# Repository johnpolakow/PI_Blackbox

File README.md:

# Raspberry Pi Based Data Acquistion System

# Directories in Repository    
## Docs/    
Contains various documentation info  created while building the software. Specification of commands to the client interface. Information on the ADC Loop, which is continuosly read out by the Raspberry Pi. Some notes on initial configuration of a Pi DAQ. Some how to files that may be useful while administrating the Pi DAQ.

## PCB/    
PI DAQ PCB Files    
Contains the files needed to FAB the Pi DAQ. All Gerber board files are present. The native Kicad project files are present as well, for maintenance and modification. There is rework required for the version of gerbers used here. The rework directions are in the **Docs/** folder. If time permits, will include a "fixed/corrected" version of the Kicad project files, eliminating the need for future rework. 

Cal Station Board Files
The PCB files for the Cal Station board are present as well, however I would not reccomend ordering this board. It was done extremely quickly and many mistakes were made. There was MUCH rework required to make the PCB functional. Almost all of the relay footprints are off. The relay part fits, but some of the pins are swapped. It was unpleasant to re-route all the signals with hookup wire, you would save yourself much time by starting over.    

All BOMS should be present as well.    

## Pi Firmware/
This folder contains the release versions of firmware that runs on the Pi DAQ. The different versions are kept for documentation and bug fixes. Also, the Configuration folder contains useful code to configure a Pi for the first time. It performs functions like:
  - Configuring hostname on the Pi
  - Configure user accounts
  - Getting / Setting Environment variables
  - Setting up alias commands for the pi user
  - setting default IP address and network configuration
  - Enabling SPI & I2C on the pi
  - Enabling SSH
  - Enable AutoLogin at boot for user pi
  - Getting the micro SD card usage stats

# Code Installation and Usage
## Source Code Download 
To download the code to the Pi, make sure you have an active internet connection on the Pi. This may involve editing the /etc/wpa_supplicant/wpa_supplicant.conf file on the Pi to add the credentials for the wifi network you want to connect to. The file will look like this:    
   
modify it by filling in the ssid of the network and the pre shared key (password) of the network.   

After conneting to Wifi/Internet, make a directory for the firmware:   
```mkdir /home/pi/firmware```   
```cd /home/pi/firmware```    
    
now clone the github repo:   
```git clone https://github.com/johnpolakow/PI_Blackbox.git```       

move everything to parent folder:         
```cd PI_Blackbox/```      
```mv -f ./* ../```     
```cd ..```
```rm -rf PI_Blackbox/```    

The PCB directory is not needed on the Pi:     
```rm -rf PCB/```     

move Docs folder to parent dir:    
```mv -f Docs/ ../```   

Change to Pi_Firmware directory and remove unnecesary releases, and move Configuration directory:      
```cd PI_Firmware/```     

Only the latest version is needed. You can remove the directories for older versions. For instance if you want to remove *Release0/* directory:    
```rm -rf Release0/```    

Move **Configuration/** directory to another location:    
```mv Configuration/ ../../```      

Last, the contents of the latest release may be moved to the firmware folder:    
```cd Release1```       
```mv -f ./* ../../```    
```cd ..```    
```rm -r Release1```    
```rm -r PI_Firmware/```     

You should now have two items in the **/home/pi/firmware/** folder:     
  - src/ folder, containing source code for compiling the DAQ executable    
  - makefile, to compile the source code    

## Compilation    
Compile the source code with the **make** command:    

the **DAQ** binary will be created. It can be executed directly with the command:     
```sudo ./DAQ```     

or, alternatively, the server process can be started with:     
```sudo systemctl restart Blackberry.service```    

check to see the process is running with the **top** command:   
```top```     
after executing the command a process display will popup. **DAQ** should be at the top:    
   
to exit out of the process display screen, hit the **q** button 

If DAQ process is not shown, then you need to either execute the DAQ process directly or start the Blackberry systemd service with:   
```sudo systemctl start Blackberry.service```

## SystemD Maintenance and Server Process Start     
 Some commands to administrate the Blackberry server process.
 see process status:        
```sudo systemctl status Blackberry.service```     

start the process:   
```sudo systemctl start Blackberry.service```    

stop the process:   
```sudo systemctl stop Blackberry.service```    

to start service at boot:    
```sudo systemctl enable [Blackberry.service]```    

view the server process file:   
```sudo systemctl cat Blackberry.service```

edit the service file:    
```sudo systemctl edit --full Blackberry.service```   

find out if the service is enabled:   
```sudo systemctl is-enabled Blackberry.service```

see log entries related only the the PI DAQ server process:   
```sudo journalctl UNIT=Blackberry.service```

```daemon-reload```

## Socket Connections    
The DAQ process opens tcp port 2020 and waits for a client to connect. To verify the port is open and listening, try these commands:    
```sudo ss -l -p | grep -vE '^(u_|nl )'```   
```sudo ss -lntu```    
```netstat -l -46```    

## Querying the Server from a Client Machine
see client code repository. Also see 'Pi_Blackbox_Software_Behavioral_Specification' in the Docs/ directory:   
https://github.com/johnpolakow/PI_Blackbox/tree/master/Docs        
https://github.com/johnpolakow/PI_Blackbox/blob/master/Docs/Pi%20Blackbox%20Software%20Behavioral%20Specification_v2.pdf     
https://github.com/johnpolakow/Blackbox_Client    

## Lessons Learned
Things I would do differently if I was to do another version of this board:     
  - Do the layout in Cadence
  - Use switching regulator to drop input of +18-24V down to +13-14V. Eliminating the need for fan and heat sink
  - Low noise *switching* regulator for Pi voltage supply. The present switching converter IC required softening of the switching waveform to get the noise down.
  - Change 2N3055 BJT based programmable current source to FET based. 
  - smaller SMD crystals
  - Use SOM instead of full Pi Board
  - High speed ADCs for Voltage and Current measurement. More accurate power metric + phase information
  - More compact electrolytic caps
  - Only use ceramic caps near LT1054 voltage inverter. Tantalum cap ended up failing due to high ESR and switching current
  - smaller input capacitance, to lower the inrush current

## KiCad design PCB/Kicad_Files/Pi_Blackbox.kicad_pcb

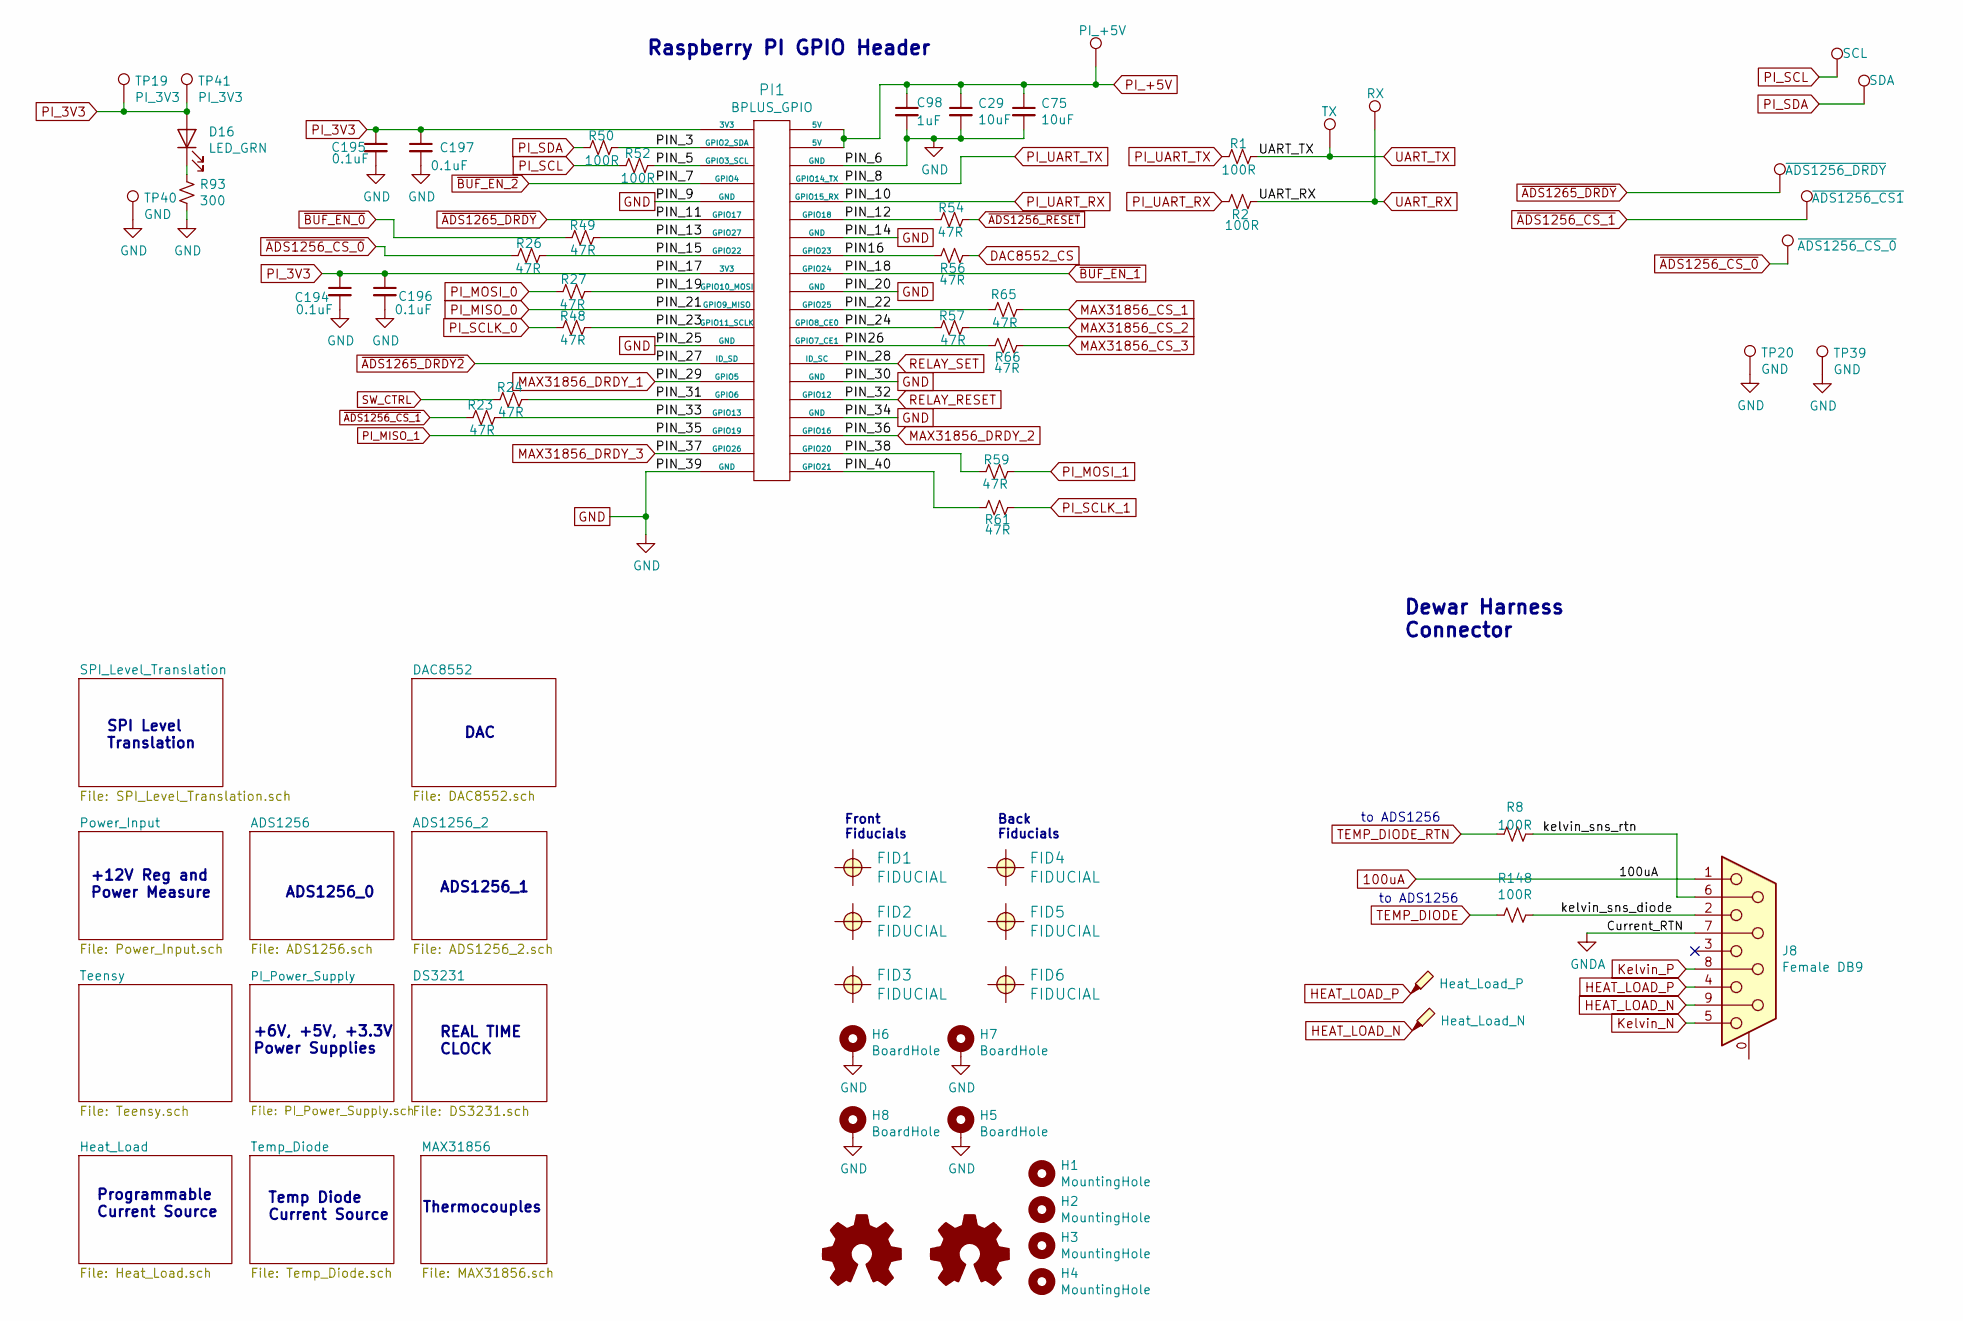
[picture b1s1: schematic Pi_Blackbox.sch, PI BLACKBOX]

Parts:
C29, C75: 10uF; C_1206_3216Metric_Pad1.42x1.75mm_HandSolder
C98: 1uF; C_0603_1608Metric_Pad1.05x0.95mm_HandSolder
C194, C195, C196, C197: 0.1uF; C_0603_1608Metric_Pad1.05x0.95mm_HandSolder
D16: LED_GRN; LED_0805_2012Metric_Pad1.15x1.40mm_HandSolder
FID1, FID2, FID4, FID5: FIDUCIAL; Fiducial_0.5mm_Mask1.5mm
FID3: FIDUCIAL; Fiducial_1.5mm_Mask3mm
FID6: FIDUCIAL; Fiducial_0.75mm_Mask2.25mm
H1, H2, H3, H4: MountingHole; MountingHole_3.5mm_Pad_Via
H5, H6, H7, H8: BoardHole; MountingHole_2.7mm_M2.5_Pad_Via
J8: Female DB9; DB9_D09S13A4GX00LF
PI1: BPLUS_GPIO; PinHeader_2x20_P2.54mm_Vertical
R1, R2, R8, R50, R52, R148: 100R; R_0402_1005Metric
R23, R24, R26, R27, R48, R49, R54, R56, R57, R59, R61, R65, R66: 47R; R_0402_1005Metric
R93: 300; R_0402_1005Metric
TP1: TX; TestPoint_Pad_D2.0mm
TP2: RX; TestPoint_Pad_D2.0mm
TP3: SCL; TestPoint_SMT_Keystone_5190
TP4: ~ADS1256_CS_0; TestPoint_SMT_Keystone_5190
TP6: SDA; TestPoint_SMT_Keystone_5190
TP13: Heat_Load_P; TestPoint_SMT_Keystone_5190
TP14: ~ADS1256_DRDY; TestPoint_SMT_Keystone_5190
TP15: ~ADS1256_CS1; TestPoint_SMT_Keystone_5190
TP19: PI_3V3; TestPoint_SMT_Keystone_5190
TP20: GND; TestPoint_Keystone_5000-5004_Miniature
TP39: GND; TestPoint_Pad_D2.0mm
TP40: GND; TestPoint_SMT_Keystone_5190
TP41: PI_3V3; TestPoint_Pad_D2.0mm
TP42: PI_+5V; TestPoint_Pad_D2.0mm
TP43: Heat_Load_N; TestPoint_SMT_Keystone_5190

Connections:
100uA: J8.1; also elsewhere on the board
/PIN16: PI1.16 (GPIO23), R56.2
/PIN26: PI1.26 (GPIO7_CE1), R66.2
/PIN_3: PI1.3 (GPIO2_SDA), R50.1
/PIN_5: PI1.5 (GPIO3_SCL), R52.1
/PIN_12: PI1.12 (GPIO18), R54.2
/PIN_13: PI1.13 (GPIO27), R49.1
/PIN_15: PI1.15 (GPIO22), R26.1
/PIN_19: PI1.19 (GPIO10_MOSI), R27.1
/PIN_22: PI1.22 (GPIO25), R65.2
/PIN_23: PI1.23 (GPIO11_SCLK), R48.1
/PIN_24: PI1.24 (GPIO8_CE0), R57.2
/PIN_31: PI1.31 (GPIO6), R24.1
/PIN_33: PI1.33 (GPIO13), R23.1
/PIN_38: PI1.38 (GPIO20), R59.2
/PIN_40: PI1.40 (GPIO21), R61.2
/kelvin_sns_diode: J8.2, R148.1
/kelvin_sns_rtn: J8.6, R8.1
DAC8552_CS: R56.1; also elsewhere on the board
GND: C29.2, C75.2, C98.2, C194.2, C195.2, C196.2, C197.2, H5.PAD, H6.PAD, H7.PAD, H8.PAD, J8.5, J8.9, PI1.6 (GND), PI1.9 (GND), PI1.14 (GND), PI1.20 (GND), PI1.25 (GND), PI1.30 (GND), PI1.34 (GND), PI1.39 (GND), R93.2, TP20.1, TP39.1, TP40.1, TP43.1; also elsewhere on the board
GNDA: J8.7; also elsewhere on the board
HEAT_LOAD_P: J8.4, J8.8, TP13.1; also elsewhere on the board
MAX31856_CS_1: R65.1; also elsewhere on the board
MAX31856_CS_2: R57.1; also elsewhere on the board
MAX31856_CS_3: R66.1; also elsewhere on the board
MAX31856_DRDY_1: PI1.29 (GPIO5); also elsewhere on the board
MAX31856_DRDY_2: PI1.36 (GPIO16); also elsewhere on the board
MAX31856_DRDY_3: PI1.37 (GPIO26); also elsewhere on the board
unnamed: D16.1 (K), R93.1
PI_3V3: C194.1, C195.1, C196.1, C197.1, D16.2 (A), PI1.1 (3V3), PI1.17 (3V3), TP19.1, TP41.1
PI_+5V: C29.1, C75.1, C98.1, PI1.2 (5V), PI1.4 (5V), TP42.1; also elsewhere on the board
PI_MISO_0: PI1.21 (GPIO9_MISO); also elsewhere on the board
PI_MISO_1: PI1.35 (GPIO19); also elsewhere on the board
PI_MOSI_0: R27.2; also elsewhere on the board
PI_MOSI_1: R59.1; also elsewhere on the board
PI_SCL: R52.2, TP3.1; also elsewhere on the board
PI_SCLK_0: R48.2; also elsewhere on the board
PI_SCLK_1: R61.1; also elsewhere on the board
PI_SDA: R50.2, TP6.1; also elsewhere on the board
PI_UART_RX: PI1.10 (GPIO15_RX), R2.2; also elsewhere on the board
PI_UART_TX: PI1.8 (GPIO14_TX), R1.2; also elsewhere on the board
RELAY_RESET: PI1.32 (GPIO12); also elsewhere on the board
RELAY_SET: PI1.28 (ID_SC); also elsewhere on the board
SW_CTRL: R24.2; also elsewhere on the board
TEMP_DIODE: R148.2; also elsewhere on the board
TEMP_DIODE_RTN: R8.2; also elsewhere on the board
UART_RX: R2.1, TP2.1
UART_TX: R1.1, TP1.1
~ADS1256_CS_0: R26.2, TP4.1; also elsewhere on the board
~ADS1256_CS_1: R23.2, TP15.1; also elsewhere on the board
~ADS1256_RESET: R54.1; also elsewhere on the board
~ADS1265_DRDY: PI1.11 (GPIO17), TP14.1; also elsewhere on the board
~ADS1265_DRDY2: PI1.27 (ID_SD); also elsewhere on the board
~BUF_EN_0: R49.2; also elsewhere on the board
~BUF_EN_1: PI1.18 (GPIO24); also elsewhere on the board
~BUF_EN_2: PI1.7 (GPIO4); also elsewhere on the board

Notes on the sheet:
Raspberry PI GPIO Header
REAL TIME CLOCK
to ADS1256
Dewar Harness Connector
Programmable Current Source
Thermocouples
DAC
ADS1256_0
ADS1256_1
+6V, +5V, +3.3V Power Supplies
Temp Diode Current Source
SPI Level Translation
+12V Reg and Power Measure
Front Fiducials
Back Fiducials

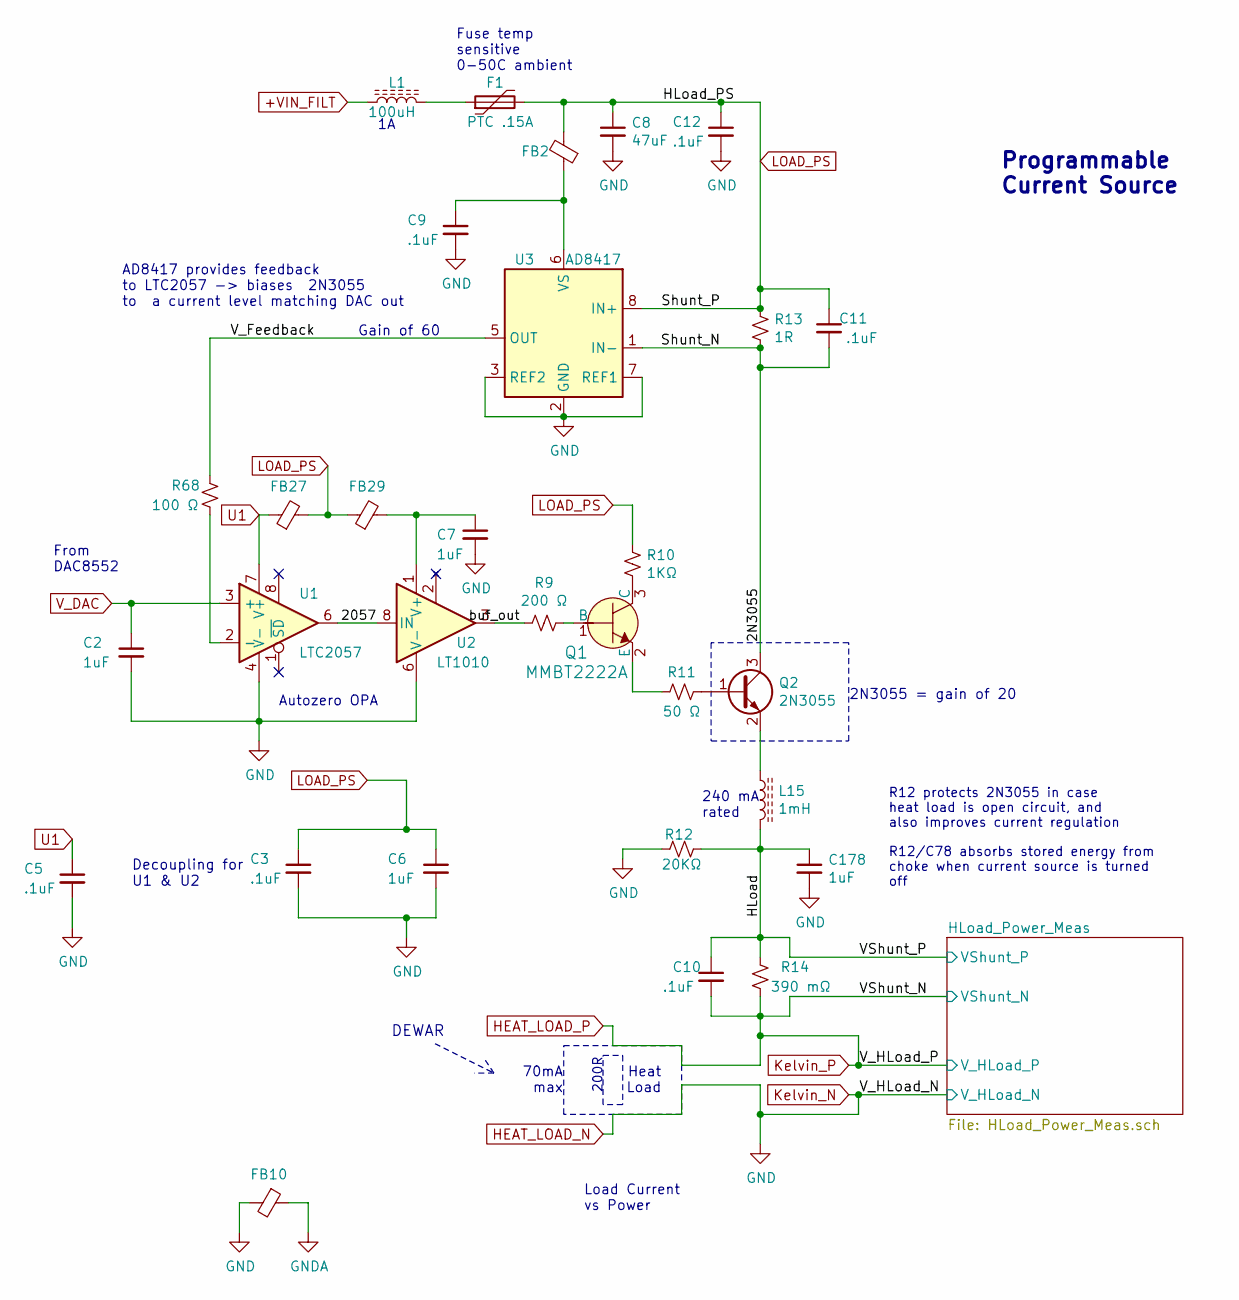
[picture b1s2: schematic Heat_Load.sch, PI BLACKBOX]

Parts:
C2, C6, C7, C178: 1uF; C_0805_2012Metric_Pad1.15x1.40mm_HandSolder
C3, C5, C9, C10, C12: .1uF; C_0603_1608Metric_Pad1.05x0.95mm_HandSolder
C8: 47uF; T495X476K035ATE300
C11: .1uF; C_0805_2012Metric_Pad1.15x1.40mm_HandSolder
F1: PTC .15A; R_1812_4532Metric_Pad1.30x3.40mm_HandSolder
FB2: FB; L_0603_1608Metric_Pad1.05x0.95mm_HandSolder
FB10: FB; L_1210_3225Metric_Pad1.42x2.65mm_HandSolder
FB27, FB29: Ferrite; C_0603_1608Metric_Pad1.05x0.95mm_HandSolder
L1: 100uH; L_Wuerth_WE-PD-Typ-LS_Handsoldering
L15: 1mH; RLB9012-222KL
Q1: MMBT2222A; SOT-23_Handsoldering; MPN MMBT2222A-7-F; Digi-Key_PN MMBT2222A-FDICT-ND
Q2: 2N3055; TO-3
R9: 200 Ω; R_0603_1608Metric_Pad1.05x0.95mm_HandSolder
R10: 1KΩ; R_0603_1608Metric_Pad1.05x0.95mm_HandSolder
R11: 50 Ω; R_0603_1608Metric_Pad1.05x0.95mm_HandSolder
R12: 20KΩ; R_0603_1608Metric_Pad1.05x0.95mm_HandSolder
R13: 1R; R_1206_3216Metric_Pad1.42x1.75mm_HandSolder
R14: 390 mΩ; R_1206_3216Metric_Pad1.42x1.75mm_HandSolder
R68: 100 Ω; R_0402_1005Metric
U1: LTC2057; SOIC-8_3.9x4.9mm_P1.27mm
U2: LT1010; DIP-8_W7.62mm_LongPads
U3: AD8417; SOIC-8_3.9x4.9mm_P1.27mm

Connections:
+VIN_FILT: L1.1; also elsewhere on the board
/Heat_Load/2N3055: C11.2, Q2.3 (C), R13.2, U3.1 (IN-)
/Heat_Load/2057: U1.6, U2.8 (IN)
/Heat_Load/HLoad: C10.1, C178.1, L15.2, R12.1, R14.1; also elsewhere on the board
/Heat_Load/V_Feedback: R68.2, U3.5 (OUT)
/Heat_Load/buf_out: R9.2, U2.3
GND: C2.2, C3.2, C5.2, C6.2, C7.2, C8.2, C9.2, C12.2, C178.2, FB10.2, R12.2, U1.4 (V-), U2.6 (V-), U3.2 (GND), U3.3 (REF2), U3.7 (REF1); also elsewhere on the board
GNDA: FB10.1; also elsewhere on the board
HEAT_LOAD_P: C10.2, R14.2; also elsewhere on the board
LOAD_PS: C3.1, C6.1, C8.1, C11.1, C12.1, F1.2, FB2.2, FB27.2, FB29.1, R10.1, R13.1, U3.8 (IN+); also elsewhere on the board
unnamed: C7.1, FB29.2, U2.1 (V+)
unnamed: C9.1, FB2.1, U3.6 (VS)
unnamed: F1.1, L1.2
unnamed: L15.1, Q2.2 (E)
unnamed: Q1.1 (B), R9.1
unnamed: Q1.2 (E), R11.2
unnamed: Q1.3 (C), R10.2
unnamed: Q2.1 (B), R11.1
unnamed: R68.1, U1.2 (-)
U1: C5.1, FB27.1, U1.7 (V+)
V_DAC: C2.1, U1.3 (+); also elsewhere on the board

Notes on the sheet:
Heat Load
From DAC8552
Autozero OPA
AD8417 provides feedback to LTC2057 -> biases 2N3055 to a current level matching DAC out
70mA max
Fuse temp sensitive 0-50C ambient
200R
Programmable Current Source
Load Current vs Power
Decoupling for U1 & U2
DEWAR
2N3055 = gain of 20
Gain of 60
240 mA rated
R12 protects 2N3055 in case heat load is open circuit, and also improves current regulation
R12/C78 absorbs stored energy from choke when current source is turned off

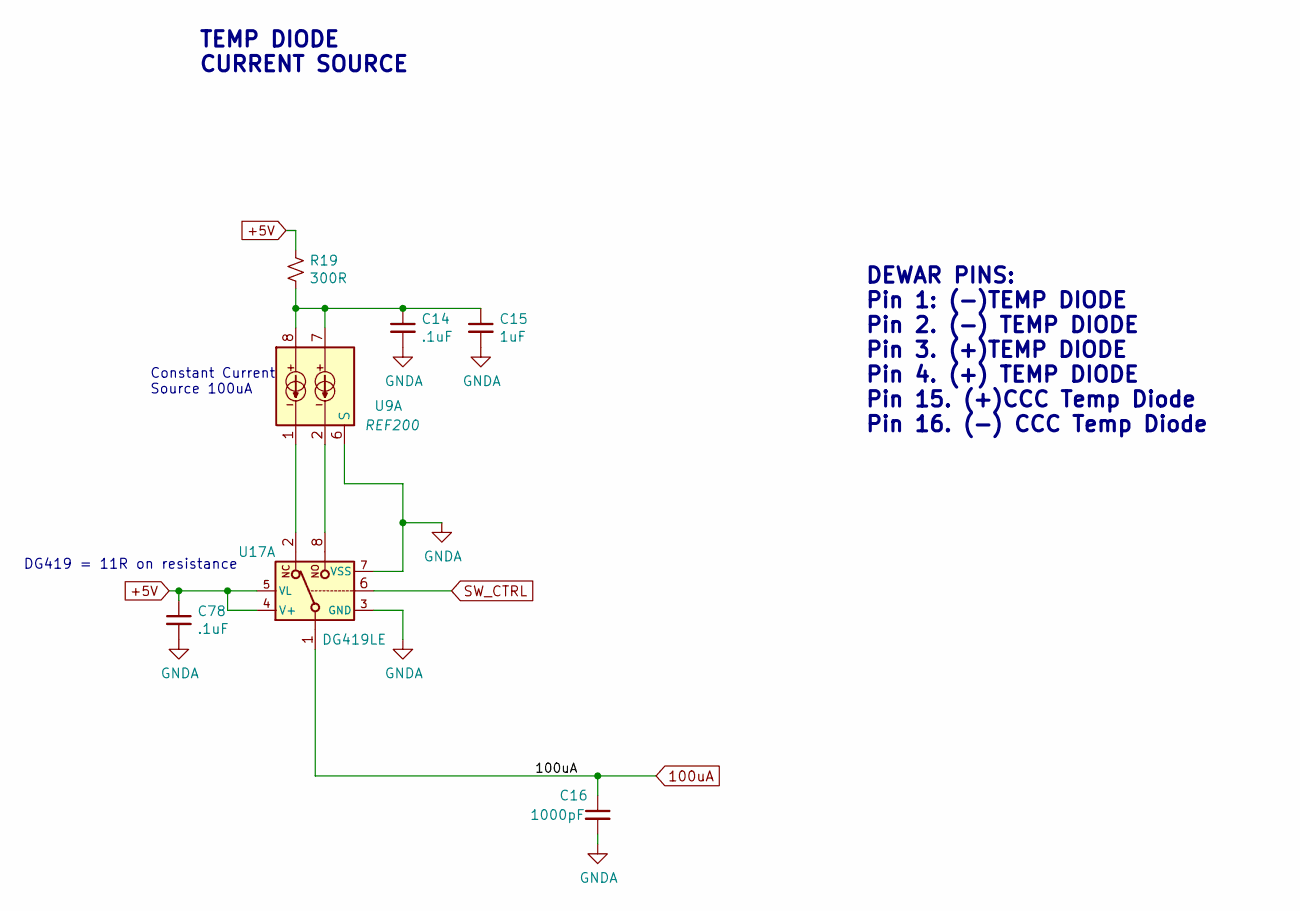
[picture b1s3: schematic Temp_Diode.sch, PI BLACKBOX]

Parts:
C14, C78: .1uF; C_0603_1608Metric_Pad1.05x0.95mm_HandSolder
C15: 1uF; C_0805_2012Metric_Pad1.15x1.40mm_HandSolder
C16: 1000pF; C_0402_1005Metric
R19: 300R; R_0603_1608Metric_Pad1.05x0.95mm_HandSolder
U9: REF200; SOIC-8_3.9x4.9mm_P1.27mm
U17: DG419LE; MSOP-8_3x3mm_P0.65mm

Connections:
100uA: C16.1, U17.1; also elsewhere on the board
+5V: C78.1, R19.1, U17.4 (V+), U17.5 (VL); also elsewhere on the board
GNDA: C14.2, C15.2, C16.2, C78.2, U9.6 (S), U17.3 (GND), U17.7 (V-); also elsewhere on the board
unnamed: C14.1, C15.1, R19.2, U9.7, U9.8
unnamed: U9.1, U17.2
unnamed: U9.2, U17.8
SW_CTRL: U17.6; also elsewhere on the board

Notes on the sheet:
Constant Current Source 100uA
TEMP DIODE CURRENT SOURCE
DG419 = 11R on resistance
DEWAR PINS: Pin 1: (-)TEMP DIODE Pin 2. (-) TEMP DIODE Pin 3. (+)TEMP DIODE Pin 4. (+) TEMP DIODE Pin 15. (+)CCC Temp Diode Pin 16. (-) CCC Temp Diode

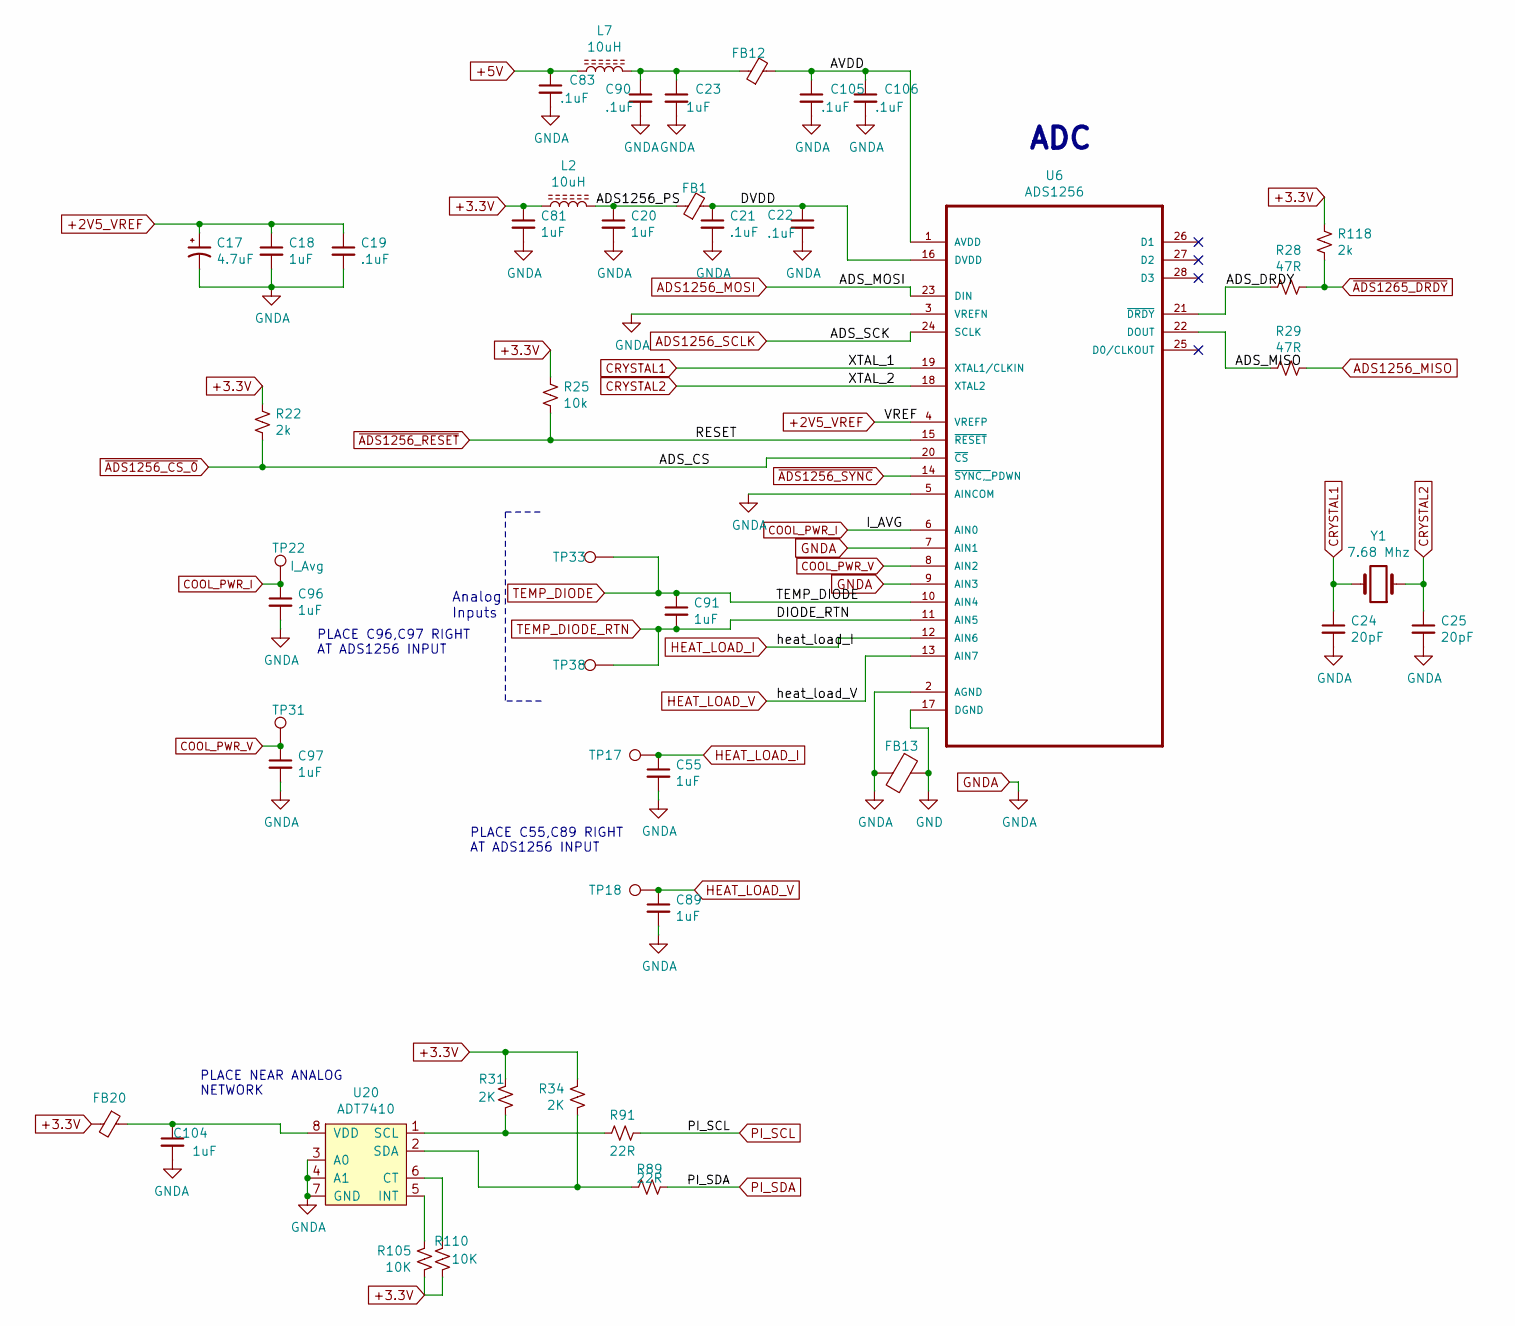
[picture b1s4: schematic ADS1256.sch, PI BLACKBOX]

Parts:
C17: 4.7uF; CP_EIA-3528-21_Kemet-B_Pad1.50x2.35mm_HandSolder
C18, C20, C55, C81, C89, C104: 1uF; C_0805_2012Metric_Pad1.15x1.40mm_HandSolder
C19, C90, C105, C106: .1uF; C_0603_1608Metric_Pad1.05x0.95mm_HandSolder
C21, C22, C83: .1uF; R_0603_1608Metric_Pad1.05x0.95mm_HandSolder
C23: 1uF; C_0603_1608Metric_Pad1.05x0.95mm_HandSolder
C24, C25: 20pF; C_0603_1608Metric_Pad1.05x0.95mm_HandSolder
C91, C96, C97: 1uF; C_1210_3225Metric_Pad1.42x2.65mm_HandSolder
FB1, FB12: FB; R_0805_2012Metric_Pad1.15x1.40mm_HandSolder
FB13: FB; L_1210_3225Metric_Pad1.42x2.65mm_HandSolder
FB20: FB; L_0805_2012Metric_Pad1.15x1.40mm_HandSolder
L2, L7: 10uH; L_1210_3225Metric_Pad1.42x2.65mm_HandSolder
R22, R118: 2k; R_0402_1005Metric
R25: 10k; R_0402_1005Metric
R28, R29: 47R; R_0402_1005Metric
R31, R34: 2K; R_0402_1005Metric
R89, R91: 22R; R_0402_1005Metric
R105, R110: 10K; R_0402_1005Metric
TP17: LOAD_I; TestPoint_SMT_Keystone_5190
TP18: LOAD_V; TestPoint_SMT_Keystone_5190
TP22: I_Avg; TestPoint_SMT_Keystone_5190
TP31: CLR_V; TestPoint_SMT_Keystone_5190
TP33: Temp_Diode; TestPoint_SMT_Keystone_5190
TP38: Diode_RTN; TestPoint_SMT_Keystone_5190
U6: ADS1256; SSOP-28_5.3x10.2mm_P0.65mm
U20: ADT7410; SOIC-8_3.9x4.9mm_P1.27mm
Y1: 7.68 Mhz; Crystal_SMD_TXC

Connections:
+2V5_VREF: C17.1, C18.1, C19.1, U6.4 (VREFP); also elsewhere on the board
+3.3V: C81.1, FB20.2, L2.1, R22.1, R25.1, R31.1, R34.1, R105.2, R110.2, R118.1; also elsewhere on the board
+5V: C83.1, L7.1; also elsewhere on the board
/ADS1256/ADS1256_PS: C20.1, FB1.1, L2.2
/ADS1256/ADS_DRDY: R28.2, U6.21 (~DRDY)
/ADS1256/ADS_MISO: R29.2, U6.22 (DOUT)
/ADS1256/AVDD: C105.1, C106.1, FB12.2, U6.1 (AVDD)
/ADS1256/DVDD: C21.1, C22.1, FB1.2, U6.16 (DVDD)
ADS1256_MISO: R29.1; also elsewhere on the board
ADS1256_MOSI: U6.23 (DIN); also elsewhere on the board
ADS1256_SCLK: U6.24 (SCLK); also elsewhere on the board
COOL_PWR_I: C96.1, TP22.1, U6.6 (AIN0); also elsewhere on the board
COOL_PWR_V: C97.1, TP31.1, U6.8 (AIN2); also elsewhere on the board
CRYSTAL1: C24.1, U6.19 (XTAL1/CLKIN), Y1.2
CRYSTAL2: C25.1, U6.18 (XTAL2), Y1.1
GND: FB13.1, U6.17 (DGND); also elsewhere on the board
GNDA: C17.2, C18.2, C19.2, C20.2, C21.2, C22.2, C23.2, C24.2, C25.2, C55.2, C81.2, C83.2, C89.2, C90.2, C96.2, C97.2, C104.2, C105.2, C106.2, FB13.2, U6.2 (AGND), U6.3 (VREFN), U6.5 (AINCOM), U6.7 (AIN1), U6.9 (AIN3), U20.3 (A0), U20.4 (A1), U20.7 (GND); also elsewhere on the board
HEAT_LOAD_I: C55.1, TP17.1, U6.12 (AIN6); also elsewhere on the board
HEAT_LOAD_V: C89.1, TP18.1, U6.13 (AIN7); also elsewhere on the board
unnamed: C23.1, C90.1, FB12.1, L7.2
unnamed: C104.1, FB20.1, U20.8 (VDD)
unnamed: R31.2, R91.2, U20.1 (SCL)
unnamed: R34.2, R89.2, U20.2 (SDA)
unnamed: R105.1, U20.5 (INT)
unnamed: R110.1, U20.6 (CT)
PI_SCL: R91.1; also elsewhere on the board
PI_SDA: R89.1; also elsewhere on the board
TEMP_DIODE: C91.1, TP33.1, U6.10 (AIN4); also elsewhere on the board
TEMP_DIODE_RTN: C91.2, TP38.1, U6.11 (AIN5); also elsewhere on the board
~ADS1256_CS_0: R22.2, U6.20 (~CS); also elsewhere on the board
~ADS1256_RESET: R25.2, U6.15 (~RESET); also elsewhere on the board
~ADS1256_SYNC: U6.14 (~SYNC,_~PDWN)
~ADS1265_DRDY: R28.1, R118.2; also elsewhere on the board

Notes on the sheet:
ADC
Analog Inputs
PLACE C96,C97 RIGHT AT ADS1256 INPUT
PLACE C55,C89 RIGHT AT ADS1256 INPUT
PLACE NEAR ANALOG NETWORK

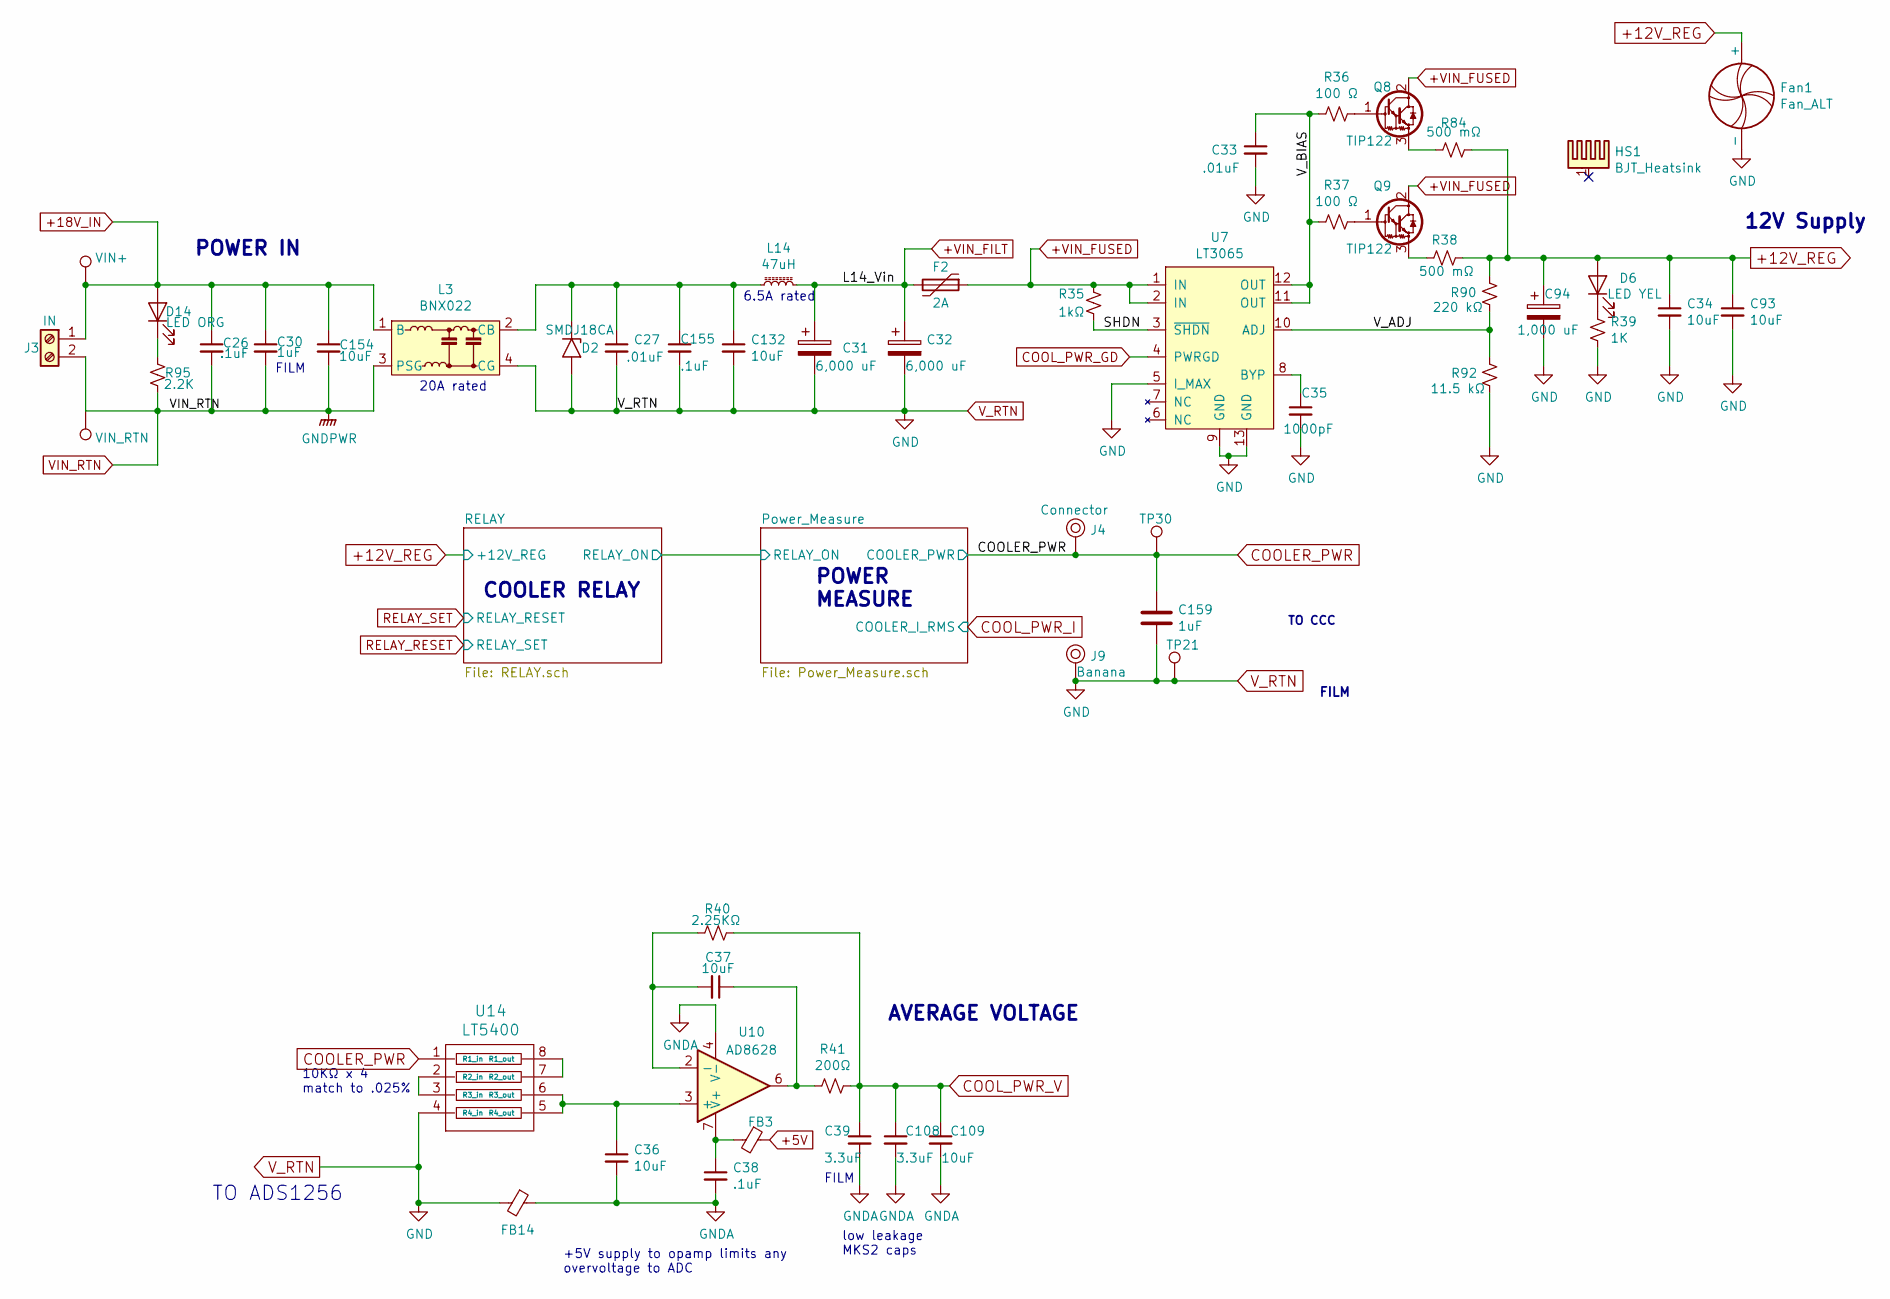
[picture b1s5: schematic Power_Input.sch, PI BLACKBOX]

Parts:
C26: .1uF; C_1206_3216Metric_Pad1.42x1.75mm_HandSolder; MFG Part # 12065C104KAT4A
C27: .01uF; C_1206_3216Metric_Pad1.42x1.75mm_HandSolder
C30: 1uF; C_Rect_L7.2mm_W7.2mm_P5.00mm_FKS2_FKP2_MKS2_MKP2
C31, C32: 6,000 uF; Chemicon_LBK_Series
C33: .01uF; C_0603_1608Metric_Pad1.05x0.95mm_HandSolder
C34, C36, C93, C109, C132, C154: 10uF; C_1206_3216Metric_Pad1.42x1.75mm_HandSolder
C35: 1000pF; C_0402_1005Metric
C37: 10uF; C_0805_2012Metric_Pad1.15x1.40mm_HandSolder
C38: .1uF; C_0603_1608Metric_Pad1.05x0.95mm_HandSolder
C39, C108: 3.3uF; C_Rect_L7.2mm_W5.5mm_P5.00mm_FKS2_FKP2_MKS2_MKP2
C94: 1,000 uF; CP_Radial_D12.5mm_P5.00mm
C155: .1uF; C_1206_3216Metric_Pad1.42x1.75mm_HandSolder
C159: 1uF; C_1210_3225Metric_Pad1.42x2.65mm_HandSolder
D2: SMDJ18CA
D6: LED YEL; LED_0805_2012Metric_Pad1.15x1.40mm_HandSolder
D14: LED ORG; LED_0805_2012Metric_Pad1.15x1.40mm_HandSolder
F2: 2A; Fuse_2920
FB3: FB; R_0805_2012Metric_Pad1.15x1.40mm_HandSolder
FB14: FB; L_1210_3225Metric_Pad1.42x2.65mm_HandSolder
Fan1: Fan_ALT; Fan_30mmx30mmx10mm
HS1: BJT_Heatsink; Heat_Sink_Omni_220-18-50-2C
J3: IN; 2-1445057-2
J4: Connector; Pomona_Banana_73099_red; MPN 105-1102-001; Digi-Key_PN J576-ND
J9: Banana; Pomona_Banana_73099; MPN 105-1102-001; Digi-Key_PN J576-ND
L3: BNX022
L14: 47uH; L_Bourns_SRP1265A
Q8, Q9: TIP122; TO-220-3_Vertical
R35: 1kΩ; R_0402_1005Metric
R36, R37: 100 Ω; R_0603_1608Metric_Pad1.05x0.95mm_HandSolder
R38, R84: 500 mΩ; R_1206_3216Metric_Pad1.42x1.75mm_HandSolder
R39: 1K; R_0402_1005Metric
R40: 2.25KΩ; R_0805_2012Metric_Pad1.15x1.40mm_HandSolder
R41: 200Ω; R_0805_2012Metric_Pad1.15x1.40mm_HandSolder
R90: 220 kΩ; R_0603_1608Metric_Pad1.05x0.95mm_HandSolder
R92: 11.5 kΩ; C_0603_1608Metric_Pad1.05x0.95mm_HandSolder
R95: 2.2K; R_0402_1005Metric
TP21: COOLER-; TestPoint_Keystone_5000-5004_Miniature
TP30: COOLER_PWR; TestPoint_Keystone_5000-5004_Miniature
TP37: VIN+; TestPoint_Keystone_5000-5004_Miniature
TP49: VIN_RTN; TestPoint_Keystone_5000-5004_Miniature
U7: LT3065; MSOP-12-1EP_3x4mm_P0.65mm_EP1.65x2.85mm_ThermalVias
U10: AD8628; SOIC-8_3.9x4.9mm_P1.27mm
U14: LT5400; MSOP-8_3x3mm_P0.65mm

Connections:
+5V: FB3.1; also elsewhere on the board
+12V_REG: C34.1, C93.1, C94.1, D6.2 (A), Fan1.1 (+), R38.1, R84.1, R90.1; also elsewhere on the board
+18V_IN: C26.1, C30.1, C154.1, D14.2 (A), J3.1, L3.1 (B), TP37.1
+VIN_FILT: C31.1, C32.1, F2.2, L14.2; also elsewhere on the board
+VIN_FUSED: F2.1, Q8.2 (C), Q9.2 (C), R35.1, U7.1 (IN), U7.2 (IN)
/Power_Input/SHDN: R35.2, U7.3 (~SHDN)
/Power_Input/V_ADJ: R90.2, R92.1, U7.10 (ADJ)
/Power_Input/V_BIAS: C33.1, R36.2, R37.2, U7.11 (OUT), U7.12 (OUT)
COOLER_PWR: C159.1, J4.1, TP30.1, U14.1 (R1_in); also elsewhere on the board
COOL_PWR_GD: U7.4 (PWRGD)
COOL_PWR_V: C39.1, C108.1, C109.1, R40.1, R41.1; also elsewhere on the board
GND: C27.2, C31.2, C32.2, C33.2, C34.2, C35.2, C93.2, C94.2, C132.2, C155.2, C159.2, D2.2 (A2), FB14.2, Fan1.2 (-), J9.1, L3.4 (CG), R39.2, R92.2, TP21.1, U7.5 (I_MAX), U7.9 (GND), U7.13 (GND), U14.4 (R4_in); also elsewhere on the board
GNDA: C36.2, C38.2, C39.2, C108.2, C109.2, FB14.1, U10.4 (V-); also elsewhere on the board
unnamed: C35.1, U7.8 (BYP)
unnamed: C36.1, U10.3 (+), U14.5 (R4_out), U14.6 (R3_out)
unnamed: C37.1, R41.2, U10.6
unnamed: C37.2, R40.2, U10.2 (-)
unnamed: C38.1, FB3.2, U10.7 (V+)
unnamed: C27.1, C132.1, C155.1, D2.1 (A1), L3.2 (CB), L14.1
unnamed: D6.1 (K), R39.1
unnamed: D14.1 (K), R95.1
unnamed: Q8.1 (B), R36.1
unnamed: Q8.3 (E), R84.2
unnamed: Q9.1 (B), R37.1
unnamed: Q9.3 (E), R38.2
unnamed: U14.2 (R2_in), U14.3 (R3_in)
unnamed: U14.7 (R2_out), U14.8 (R1_out)
VIN_RTN: C26.2, C30.2, C154.2, J3.2, L3.3 (PSG), R95.2, TP49.1

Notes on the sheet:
12V Supply
COOLER RELAY
+5V supply to opamp limits any overvoltage to ADC
10KΩ x 4 match to .025%
low leakage MKS2 caps
TO ADS1256
AVERAGE VOLTAGE
POWER IN
20A rated
6.5A rated
FILM
FILM
POWER MEASURE
TO CCC

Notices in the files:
parts and their libraries:
Copyright 2016 Accelerated Designs. All rights reserved.
